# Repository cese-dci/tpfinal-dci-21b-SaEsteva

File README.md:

## Trabajo práctico final de la asignatura DCI ##
Este repositorio contiene el trabajo práctico final para la asignatura de Diseño de Circuitos Impresos de la carrera de posgrado de FIUBA.

* Autor: SANTIAGO ESTEVA
* Título corto del trabajo:  Réplica Modulo Ethernet Enc28j60
* Descripción:  El módulo Ethernet ENC28J60 utiliza el Ethernet Controller de Microchip. Ofrece una serie de funciones para manejar la mayor parte de los requisitos del protocolo de red. El módulo se conecta directamente a la mayoría de los microcontroladores con interfaz SPI estándar con una velocidad de transferencia de hasta 20MHz.

## Licencia de este trabajo ##
Este producto es de código abierto !

El hardware es liberado bajo [Creative Commons ShareAlike 4.0 International](https://creativecommons.org/licenses/by-sa/4.0/).

El código es beerware; Si encuentra útil este código, ¡cómpreme una medualuna!

Utilice, reutilice y modifique estos archivos como mejor le parezca. Mantenga la atribución a Santiago Esteva y libere cualquier derivado bajo la misma licencia.

Distribuido como está; no se da ninguna garantía.

Tu amigo Santiago Esteva.

## Estructura del TP FINAL ##

Se propone y se pide utilizar la siguiente estructura.

* doc: Toda la información sobre el circuito, principalmente de autoría o procesamiento propio. Por ejemplo:
  * Notas de ingeniería propias.
  * Notas de aplicación propias.
  * Estudios previos, estado del arte, resumen de las investigaciones.
  * Notas con cálculos.
  * Dibujos adicionales.
  * Fotos de los prototipos.
  * Presupuestos, cotizaciones.
* info: Toda la iformación recolectada, principalmente de terceros, como por ejemplo:
  * Hojas de datos.
  * Notas de aplicación.
  * Info de productos comerciales.
  * Info en internet.
* pcb: Archivos de diseño esquemático y pcb.

Dependiendo la magnitud del proyecto, tendremos más o menos información en estos directorios. 
Revisar los README.md en cada directorio para conocer las pautas de cada uno para este TP.

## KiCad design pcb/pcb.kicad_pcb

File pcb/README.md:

## Archivos Kicad ##

En este directorio se encuentra:

* Archivos de proyecto.
* Esquemático.
* PCB.
* Modelos  3D.
* Bibliotecas de símbolos y huellas externas (si son necesarios).

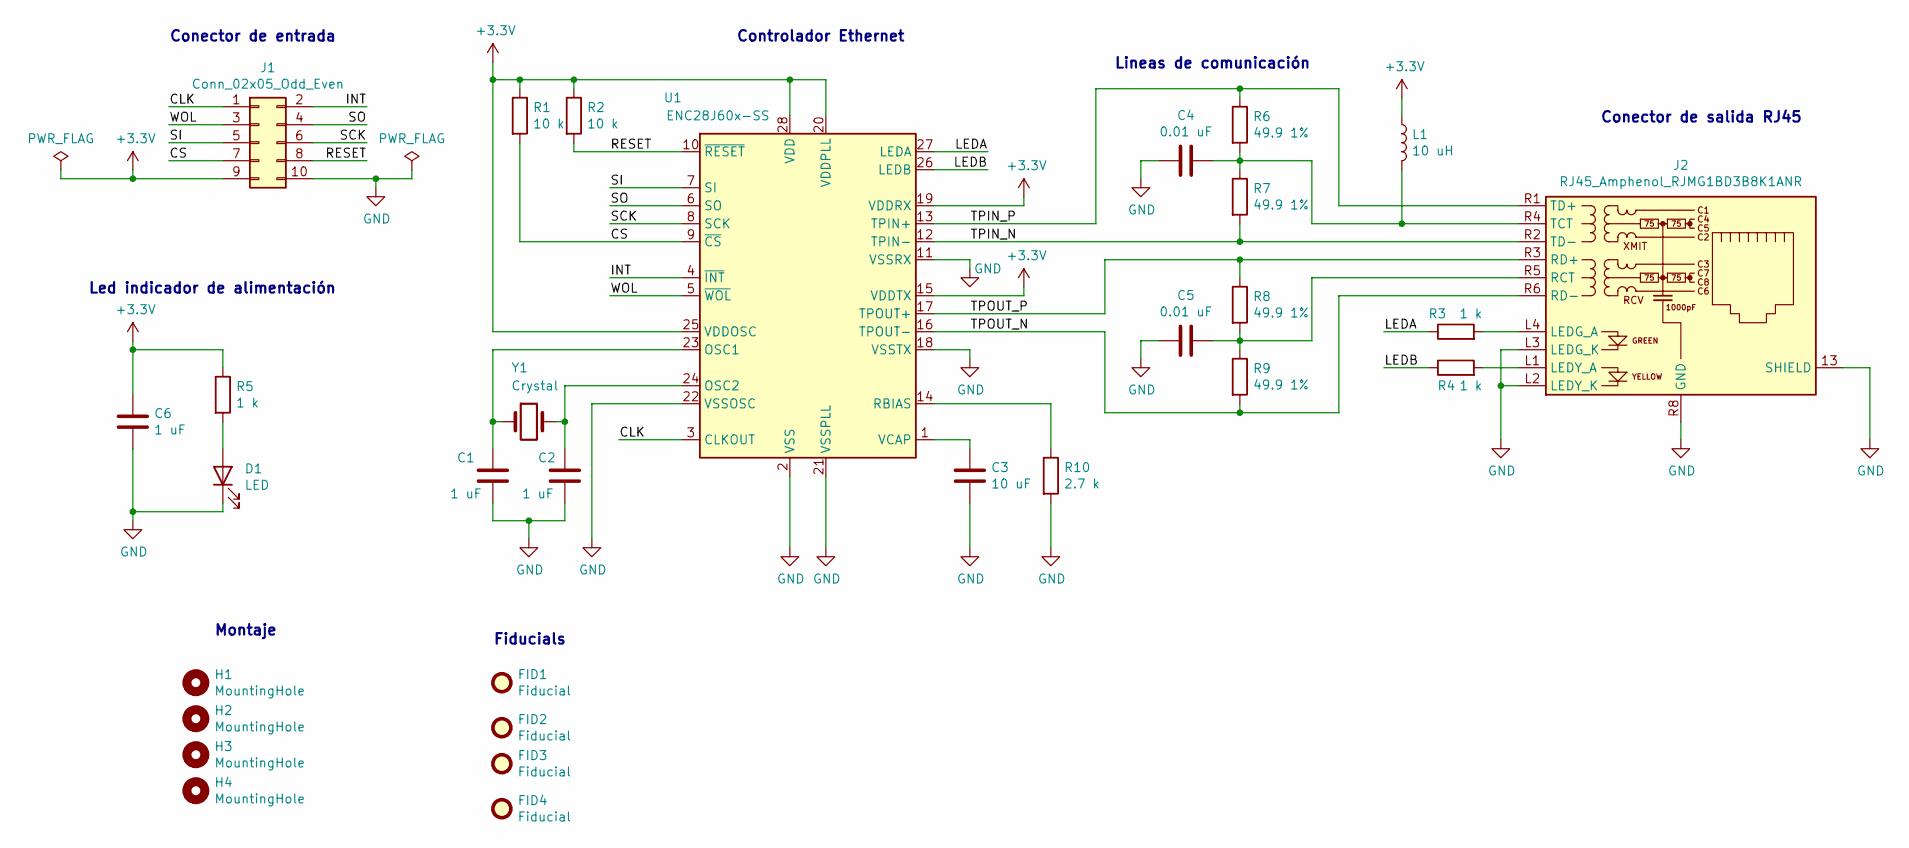
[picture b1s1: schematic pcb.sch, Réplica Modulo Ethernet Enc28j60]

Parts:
C1, C2, C6: 1 uF; C_0805_2012Metric_Pad1.18x1.45mm_HandSolder; Manufacturer Part no. JMK105BJ105KV-F
C3: 10 uF; C_0805_2012Metric_Pad1.18x1.45mm_HandSolder; Manufacturer Part no. 81-GRM155R60J106M05D
C4, C5: 0.01 uF; C_0805_2012Metric_Pad1.18x1.45mm_HandSolder; Manufacturer Part no. UMF105B7103MVHF
D1: LED; LED_0805_2012Metric_Pad1.15x1.40mm_HandSolder; Manufacturer Part no. LS R976-NR-1
FID1, FID2, FID3, FID4: Fiducial; Fiducial_0.5mm_Mask1mm
H1, H2, H3, H4: MountingHole; MountingHole_2.2mm_M2_DIN965_Pad
J1: Conn_02x05_Odd_Even; PinHeader_2x05_P2.00mm_Vertical; Manufacturer Part no. 10129381-910001BLF
J2: RJ45_Amphenol_RJMG1BD3B8K1ANR; Manufacturer Part no. RJMG1BD3B8K1ANR
L1: 10 uH; L_0805_2012Metric_Pad1.05x1.20mm_HandSolder; Manufacturer Part no. L0805R100MPWST
R1, R2: 10 k; R_0805_2012Metric_Pad1.20x1.40mm_HandSolder; Manufacturer Part no. CRCW080510K0JNEAC
R3, R4, R5: 1 k; R_0805_2012Metric_Pad1.20x1.40mm_HandSolder; Manufacturer Part no. RMC1/10K1001FTP
R6, R7, R8, R9: 49.9 1%; R_0805_2012Metric_Pad1.20x1.40mm_HandSolder; Manufacturer Part no. ERJ-6RED49R9V
R10: 2.7 k; R_0805_2012Metric_Pad1.20x1.40mm_HandSolder; Manufacturer Part no. RMC1/10K2671FTP
U1: ENC28J60x-SS; SSOP-28_5.3x10.2mm_P0.65mm; Manufacturer Part no. ENC28J60/SS
Y1: Crystal; Crystal_HC49-4H_Vertical; Manufacturer Part no. HC-49/U-S25000000ABJB

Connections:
+3V3: C6.1, J1.9, L1.1, R1.1, R2.1, R5.1, U1.15 (VDDTX), U1.19 (VDDRX), U1.20 (VDDPLL), U1.25 (VDDOSC), U1.28 (VDD); also elsewhere on the board
/CLK: J1.1, U1.3 (CLKOUT); also elsewhere on the board
/CS: J1.7, R1.2, U1.9 (~CS); also elsewhere on the board
/INT: J1.2, U1.4 (~INT); also elsewhere on the board
/LEDA: R3.1, U1.27 (LEDA)
/LEDB: R4.1, U1.26 (LEDB)
/RESET: J1.8, R2.2, U1.10 (~RESET); also elsewhere on the board
/SCK: J1.6, U1.8 (SCK); also elsewhere on the board
/SI: J1.5, U1.7 (SI); also elsewhere on the board
/SO: J1.4, U1.6 (SO); also elsewhere on the board
/WOL: J1.3, U1.5 (~WOL); also elsewhere on the board
GND: C1.2, C2.1, C3.2, C4.2, C5.2, C6.2, D1.1 (K), J1.10, J2.13 (SHIELD), J2.L2 (LEDY_K), J2.L3 (LEDG_K), J2.R8 (GND), R10.2, U1.2 (VSS), U1.11 (VSSRX), U1.18 (VSSTX), U1.21 (VSSPLL), U1.22 (VSSOSC); also elsewhere on the board
unnamed: C1.1, U1.23 (OSC1), Y1.1
unnamed: C2.2, U1.24 (OSC2), Y1.2
unnamed: C3.1, U1.1 (VCAP)
unnamed 15: C4.1, J2.R4 (TCT), L1.2, R6.2, R7.1; also elsewhere on the board
unnamed 16: C5.1, J2.R5 (RCT), R8.2, R9.1; also elsewhere on the board
unnamed: D1.2 (A), R5.2
unnamed 18: J2.L1 (LEDY_A), R4.2; also elsewhere on the board
unnamed 19: J2.L4 (LEDG_A), R3.2; also elsewhere on the board
unnamed 20: J2.R1 (TD+), R6.1, U1.13 (TPIN+); also elsewhere on the board
unnamed 21: J2.R2 (TD-), R7.2, U1.12 (TPIN-); also elsewhere on the board
unnamed 22: J2.R3 (RD+), R8.1, U1.17 (TPOUT+); also elsewhere on the board
unnamed 23: J2.R6 (RD-), R9.2, U1.16 (TPOUT-); also elsewhere on the board
unnamed: R10.1, U1.14 (RBIAS)

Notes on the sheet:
Conector de entrada
Controlador Ethernet
Conector de salida RJ45
Led indicador de alimentación
Montaje
Fiducials
Lineas de comunicación

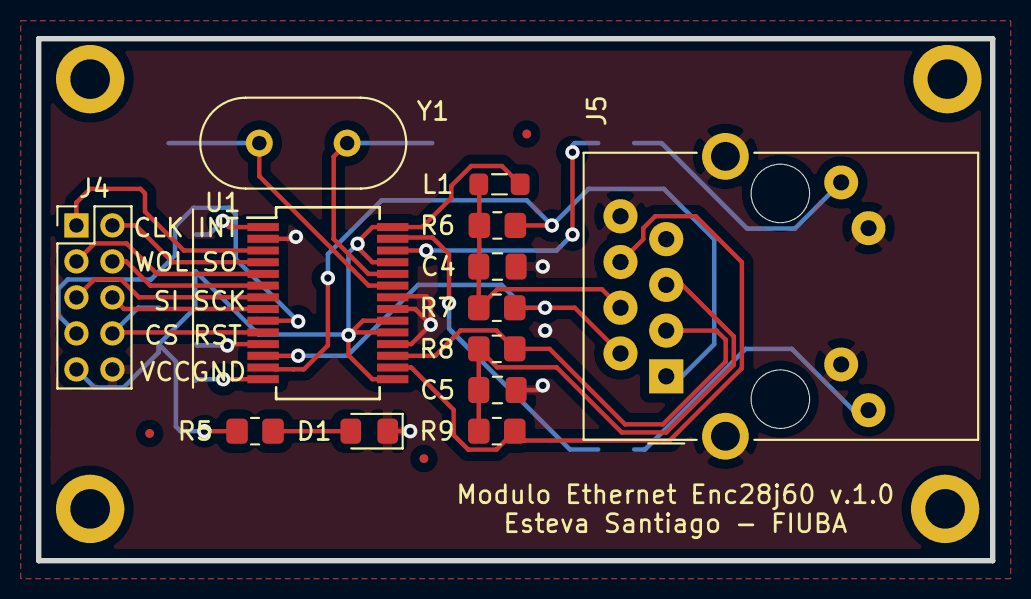
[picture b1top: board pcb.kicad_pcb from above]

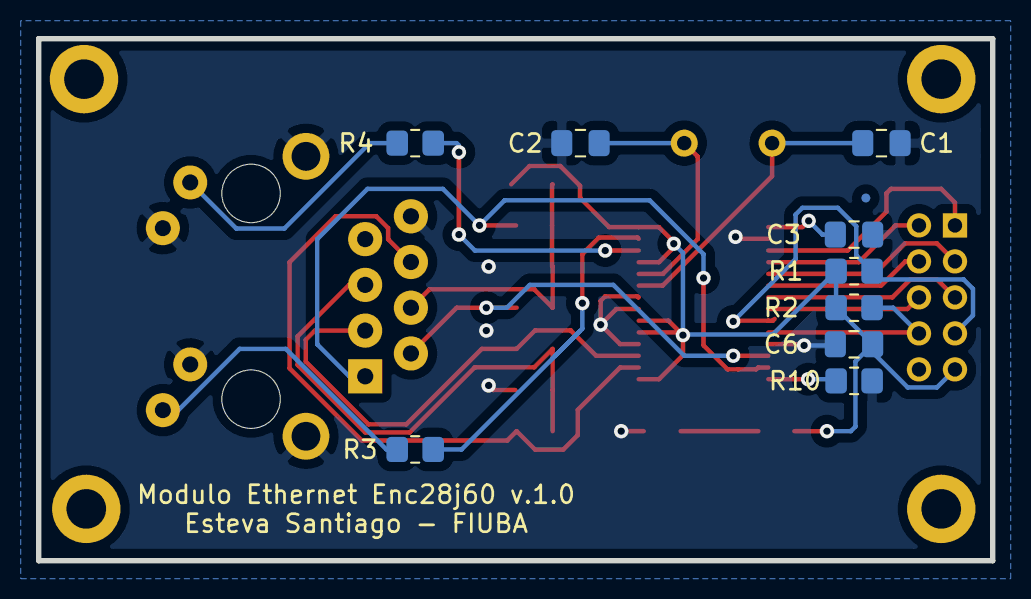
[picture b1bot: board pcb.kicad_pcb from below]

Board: 2 copper layers, 53.0 x 29.0 mm, 30 parts (10 on the bottom side), 25 nets.

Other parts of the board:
J4: Conn_02x05_Odd_Even; PinHeader_2x05_P2.00mm_Vertical
J5: RJ45_Amphenol_RJMG1BD3B8K1ANR

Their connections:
+3V3: J4.9; also elsewhere on the board
/CLK: J4.1; also elsewhere on the board
/CS: J4.7; also elsewhere on the board
/INT: J4.2; also elsewhere on the board
/RESET: J4.8; also elsewhere on the board
/SCK: J4.6; also elsewhere on the board
/SI: J4.5; also elsewhere on the board
/SO: J4.4; also elsewhere on the board
/WOL: J4.3; also elsewhere on the board
GND: J4.10, J5.13, J5.L2, J5.L3, J5.R8; also elsewhere on the board
unnamed 15: J5.R4; also elsewhere on the board
unnamed 16: J5.R5; also elsewhere on the board
unnamed 18: J5.L1; also elsewhere on the board
unnamed 19: J5.L4; also elsewhere on the board
unnamed 20: J5.R1; also elsewhere on the board
unnamed 21: J5.R2; also elsewhere on the board
unnamed 22: J5.R3; also elsewhere on the board
unnamed 23: J5.R6; also elsewhere on the board

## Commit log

2021-07-12 ruteo de PCB con DRC sin errores
2021-07-26 Agrego modelo 3D de conector RJ45
2021-07-27 Corrección de pin de montaje
2021-08-02 cambios en readme
2021-08-08 Correcciones
2021-08-08 Corrección chica
2021-08-08 Cambios en rótulo
2021-08-08 Corrección
2021-08-10 Mejoras en diseño
2021-08-16 Correcciones finales para la presentación
2021-08-16 cambio de fecha en rótulo de PCB
2021-08-16 correcciones durante la exposición
